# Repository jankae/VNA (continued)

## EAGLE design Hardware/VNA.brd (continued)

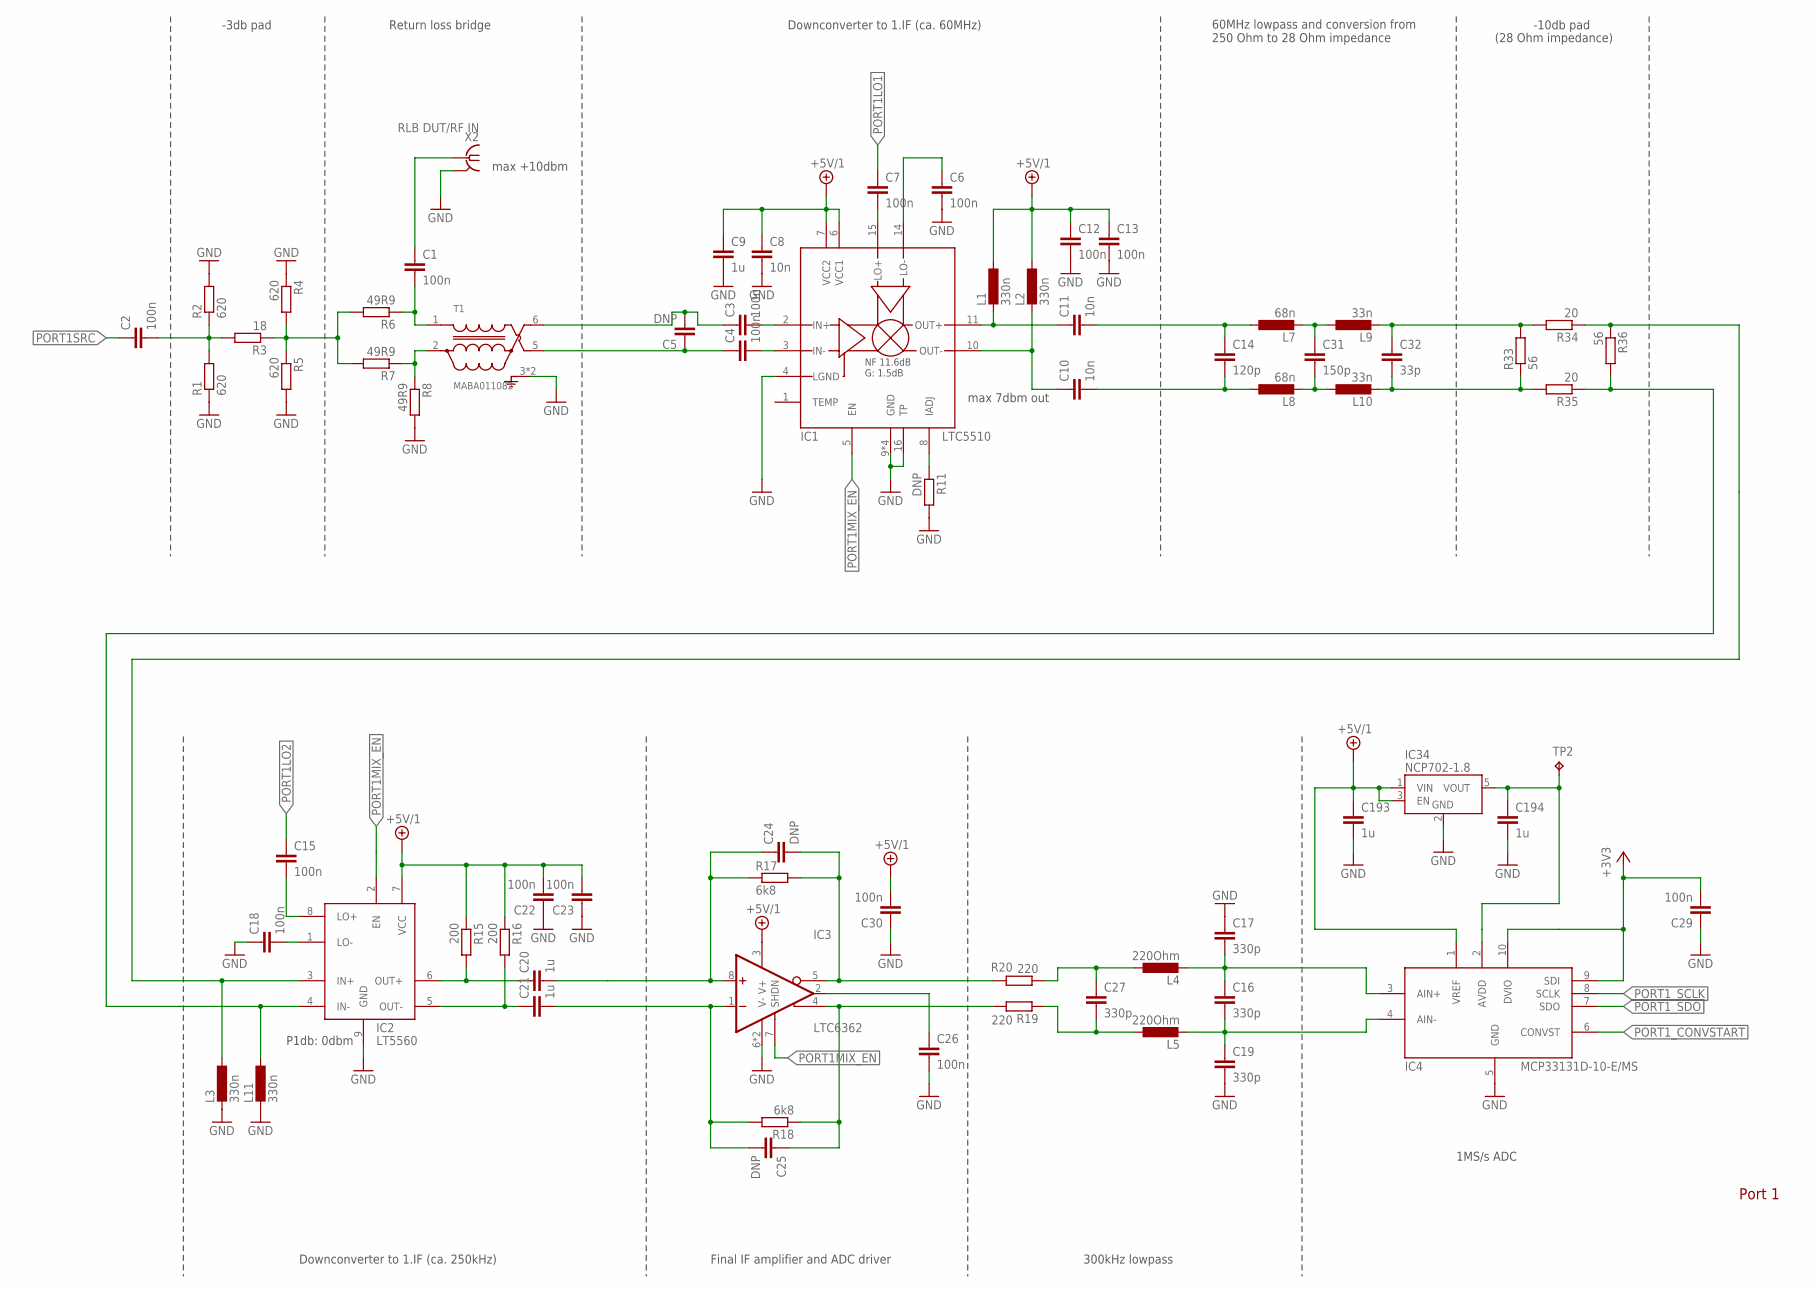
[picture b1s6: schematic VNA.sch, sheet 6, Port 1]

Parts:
C1, C2, C3, C4, C6, C7, C12, C13, C15, C18, C22, C23, C26, C29, C30: 100n; C0603
C5, C24, C25: DNP; C0603
C8, C10, C11: 10n; C0603
C9, C20, C21, C193, C194: 1u; C0603
C14: 120p; C0603
C16, C17, C19, C27: 330p; C0603
C31: 150p; C0603
C32: 33p; C0603
IC1: LTC5510; QFN65P400X400X75-17T215N
IC2: LT5560; SON50P300X300X80-9T165X238
IC3: LTC6362; SON50P300X300X80-9T165X238
IC4: MCP33131D-10-E/MS; SOP50P490X110-10N
IC34: NCP702-1.8; SOT95P240X110-5
L1, L2, L3, L11: 330n; R0603
L4, L5: 220Ohm; R0603
L7, L8: 68n; R0603
L9, L10: 33n; R0603
R1, R2, R4, R5: 620; R0603
R3: 18; R0603
R6, R7, R8: 49R9; R0603
R11: DNP; R0603
R15, R16: 200; R0603
R17, R18: 6k8; R0603
R19, R20: 220; R0603
R33, R36: 56; R0603
R34, R35: 20; R0603
T1: MABA011082; MACOM_BALUN
TP2: TPB1,27; B1,27
X2: RLB DUT/RF IN; J502-ND-142-0711-821/826

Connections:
+3V3: C29.2, IC4.9 (SDI), IC4.10 (DVIO); also elsewhere on the board
+5V/1: C8.1, C9.1, C12.1, C13.1, C22.2, C23.2, C30.2, C193.1, IC1.6 (VCC1), IC1.7 (VCC2), IC2.7 (VCC), IC3.3 (V+), IC4.1 (VREF), IC34.1 (VIN), IC34.3 (EN), L1.1, L2.1, R15.1, R16.1; also elsewhere on the board
GND: C6.2, C8.2, C9.2, C12.2, C13.2, C17.1, C18.1, C19.2, C22.1, C23.1, C26.2, C29.1, C30.1, C193.2, C194.2, IC1.4 (LGND), IC1.9 (GND), IC1.12 (GND), IC1.13 (GND), IC1.16 (TP), IC1.17 (GND), IC2.9 (GND), IC3.6 (V-), IC3.9 (V-), IC4.5 (GND), IC34.2 (GND), L3.2, L11.2, R1.1, R2.2, R4.1, R5.2, R8.2, R11.2, T1.3 (GND), T1.4 (GND), X2.G@1 (2), X2.G@2 (2), X2.G@3 (2), X2.G@4 (2); also elsewhere on the board
unnamed: C2.2, R1.2, R2.1, R3.2
unnamed: R3.1, R4.2, R5.1, R6.2, R7.2
unnamed: C11.2, C14.1, L7.1
unnamed: C1.2, R6.1, T1.1 (PIN1)
unnamed: R7.1, R8.1, T1.2 (PIN2)
unnamed: C1.1, X2.1
unnamed: C3.2, IC1.2 (IN+)
unnamed: C4.2, IC1.3 (IN-)
unnamed: C4.1, C5.1, T1.5 (PIN5)
unnamed: C3.1, C5.2, T1.6 (PIN6)
unnamed: C6.1, IC1.14 (LO-)
unnamed: C7.2, IC1.15 (LO+)
unnamed: C16.1, C17.2, IC4.3 (AIN+), L4.2
unnamed: C11.1, IC1.11 (OUT+), L1.2
unnamed: C10.1, IC1.10 (OUT-), L2.2
unnamed: C10.2, C14.2, L8.1
unnamed: C31.2, L8.2, L10.1
unnamed: C15.2, IC2.8 (LO+)
unnamed: IC1.8 (IADJ), R11.1
unnamed: C16.2, C19.1, IC4.4 (AIN-), L5.2
unnamed: C18.2, IC2.1 (LO-)
unnamed: C20.1, IC2.6 (OUT+), R15.2
unnamed: C21.1, IC2.5 (OUT-), R16.2
unnamed: C25.1, IC3.4 (+OUT), R18.1, R19.2
unnamed: C24.2, IC3.5 (-OUT), R17.2, R20.2
unnamed: C31.1, L7.2, L9.1
unnamed: IC2.3 (IN+), L3.1, R34.1, R36.1
unnamed: C32.1, L9.2, R33.2, R34.2
unnamed: C32.2, L10.2, R33.1, R35.2
unnamed: IC2.4 (IN-), L11.1, R35.1, R36.2
unnamed: C21.2, C25.2, IC3.1 (-IN), R18.2
unnamed: C20.2, C24.1, IC3.8 (+IN), R17.1
unnamed: C194.1, IC4.2 (AVDD), IC34.5 (VOUT), TP2.TP
OUT+: C27.1, L4.1, R20.1
OUT-: C27.2, L5.1, R19.1
OUT_CM: C26.1, IC3.2 (VOCM)
PORT1LO1: C7.1; also elsewhere on the board
PORT1LO2: C15.1; also elsewhere on the board
PORT1MIX_EN: IC1.5 (EN), IC2.2 (EN), IC3.7 (SHDN); also elsewhere on the board
PORT1SRC: C2.1; also elsewhere on the board
PORT1_CONVSTART: IC4.6 (CONVST); also elsewhere on the board
PORT1_SCLK: IC4.8 (SCLK); also elsewhere on the board
PORT1_SDO: IC4.7 (SDO); also elsewhere on the board

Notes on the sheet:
max +10dbm
max 7dbm out
P1db: 0dbm
-3db pad
Return loss bridge
Downconverter to 1.IF (ca. 60MHz)
60MHz lowpass and conversion from 250 Ohm to 28 Ohm impedance
-10db pad
(28 Ohm impedance)
Downconverter to 1.IF (ca. 250kHz)
Final IF amplifier and ADC driver
300kHz lowpass
1MS/s ADC
Port 1

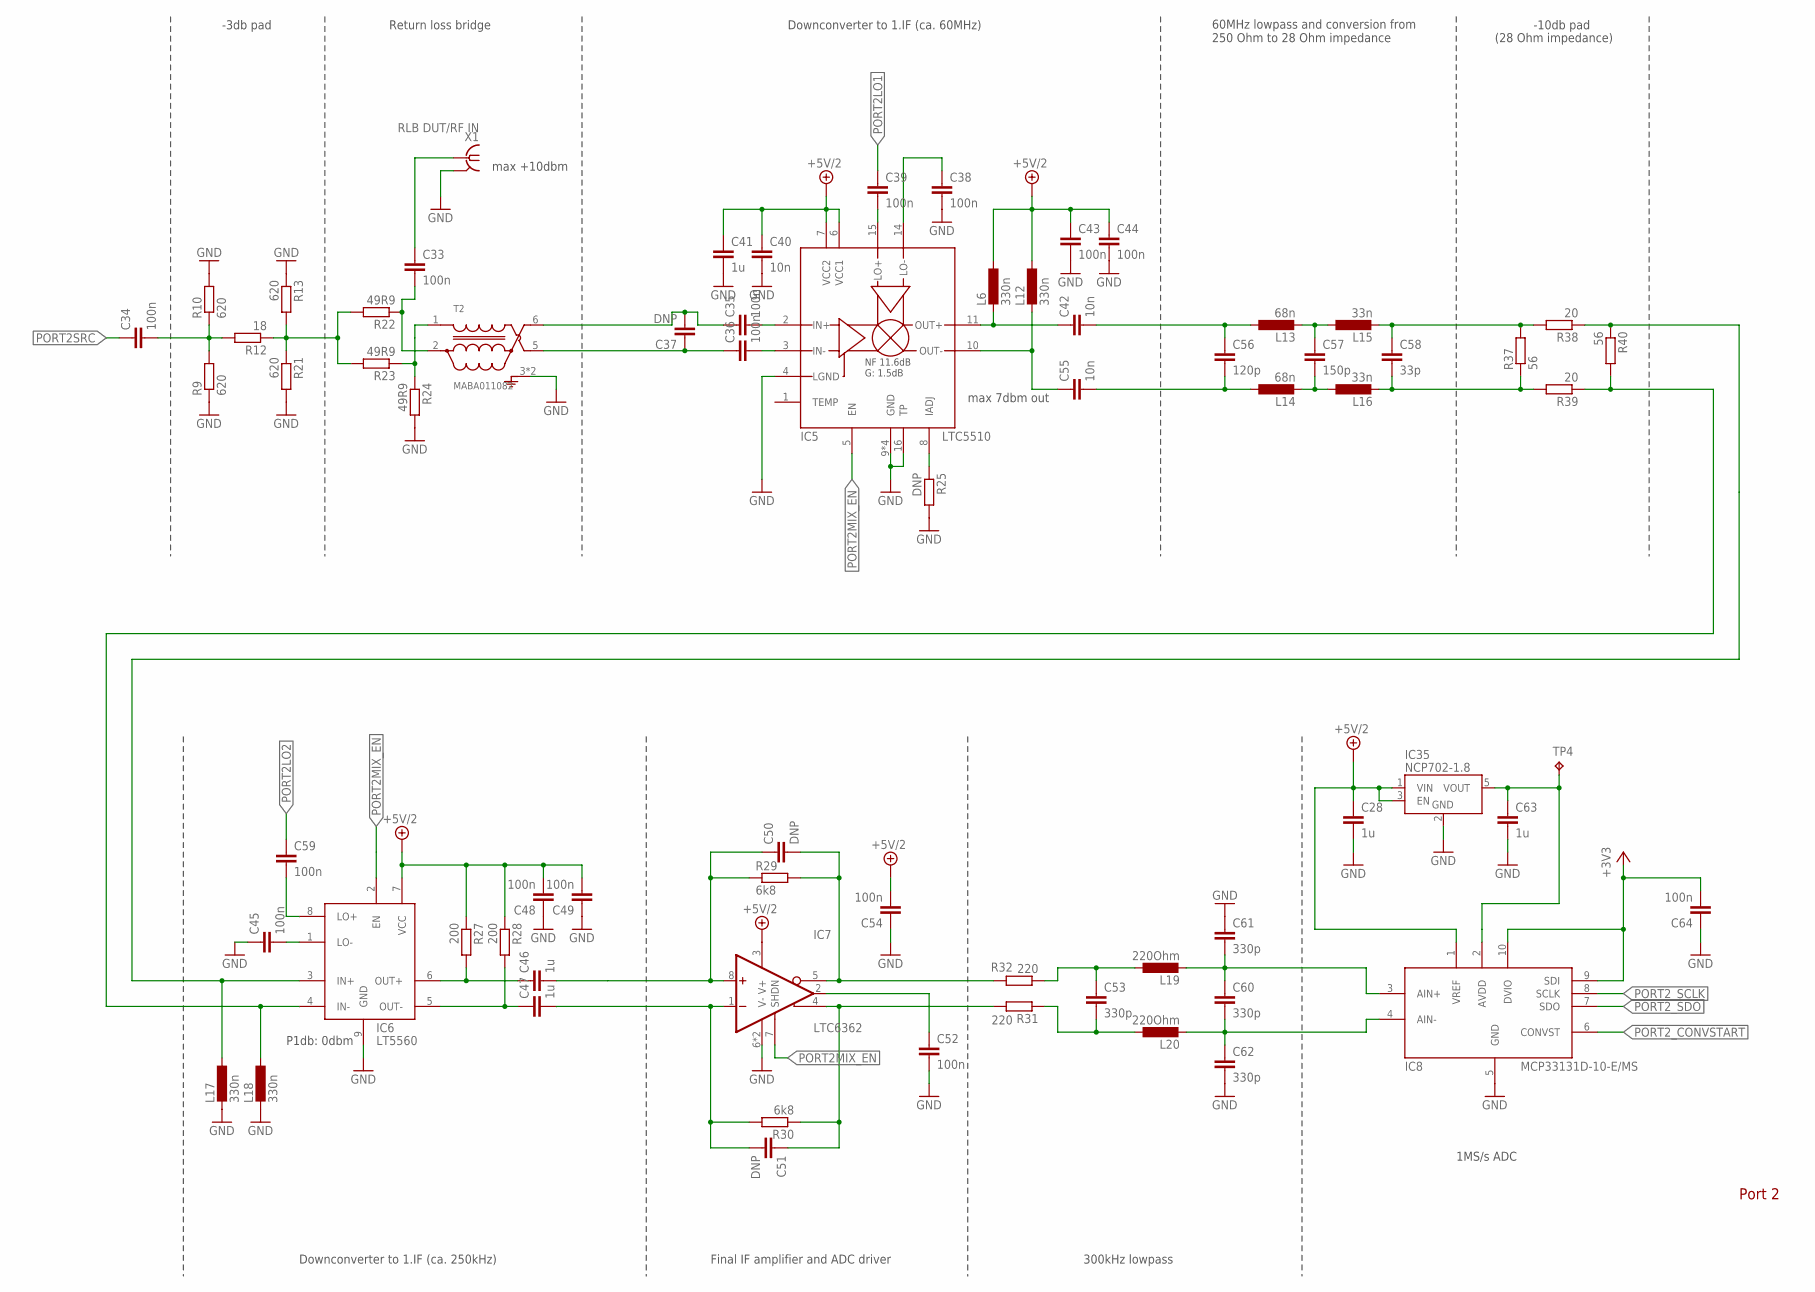
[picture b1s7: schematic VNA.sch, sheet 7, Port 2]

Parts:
C28, C41, C46, C47, C63: 1u; C0603
C33, C34, C35, C36, C38, C39, C43, C44, C45, C48, C49, C52, C54, C59, C64: 100n; C0603
C37, C50, C51: DNP; C0603
C40, C42, C55: 10n; C0603
C53, C60, C61, C62: 330p; C0603
C56: 120p; C0603
C57: 150p; C0603
C58: 33p; C0603
IC5: LTC5510; QFN65P400X400X75-17T215N
IC6: LT5560; SON50P300X300X80-9T165X238
IC7: LTC6362; SON50P300X300X80-9T165X238
IC8: MCP33131D-10-E/MS; SOP50P490X110-10N
IC35: NCP702-1.8; SOT95P240X110-5
L6, L12, L17, L18: 330n; R0603
L13, L14: 68n; R0603
L15, L16: 33n; R0603
L19, L20: 220Ohm; R0603
R9, R10, R13, R21: 620; R0603
R12: 18; R0603
R22, R23, R24: 49R9; R0603
R25: DNP; R0603
R27, R28: 200; R0603
R29, R30: 6k8; R0603
R31, R32: 220; R0603
R37, R40: 56; R0603
R38, R39: 20; R0603
T2: MABA011082; MACOM_BALUN
TP4: TPB1,27; B1,27
X1: RLB DUT/RF IN; J502-ND-142-0711-821/826

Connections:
+3V3: C64.2, IC8.9 (SDI), IC8.10 (DVIO); also elsewhere on the board
+5V/2: C28.1, C40.1, C41.1, C43.1, C44.1, C48.2, C49.2, C54.2, IC5.6 (VCC1), IC5.7 (VCC2), IC6.7 (VCC), IC7.3 (V+), IC8.1 (VREF), IC35.1 (VIN), IC35.3 (EN), L6.1, L12.1, R27.1, R28.1; also elsewhere on the board
GND: C28.2, C38.2, C40.2, C41.2, C43.2, C44.2, C45.1, C48.1, C49.1, C52.2, C54.1, C61.1, C62.2, C63.2, C64.1, IC5.4 (LGND), IC5.9 (GND), IC5.12 (GND), IC5.13 (GND), IC5.16 (TP), IC5.17 (GND), IC6.9 (GND), IC7.6 (V-), IC7.9 (V-), IC8.5 (GND), IC35.2 (GND), L17.2, L18.2, R9.1, R10.2, R13.1, R21.2, R24.2, R25.2, T2.3 (GND), T2.4 (GND), X1.G@1 (2), X1.G@2 (2), X1.G@3 (2), X1.G@4 (2); also elsewhere on the board
unnamed: C34.2, R9.2, R10.1, R12.2
unnamed: R12.1, R13.2, R21.1, R22.2, R23.2
unnamed: C33.2, R22.1, T2.2 (PIN2)
unnamed: R23.1, R24.1, T2.1 (PIN1)
unnamed: C33.1, X1.1
unnamed: C35.2, IC5.2 (IN+)
unnamed: C36.2, IC5.3 (IN-)
unnamed: C36.1, C37.1, T2.5 (PIN5)
unnamed: C35.1, C37.2, T2.6 (PIN6)
unnamed: C38.1, IC5.14 (LO-)
unnamed: C39.2, IC5.15 (LO+)
unnamed: C42.1, IC5.11 (OUT+), L6.2
unnamed: C55.1, IC5.10 (OUT-), L12.2
unnamed: IC5.8 (IADJ), R25.1
unnamed: C45.2, IC6.1 (LO-)
unnamed: C46.1, IC6.6 (OUT+), R27.2
unnamed: C47.1, IC6.5 (OUT-), R28.2
unnamed: C51.1, IC7.4 (+OUT), R30.1, R31.2
unnamed: C50.2, IC7.5 (-OUT), R29.2, R32.2
unnamed: C42.2, C56.1, L13.1
unnamed: C55.2, C56.2, L14.1
unnamed: C57.2, L14.2, L16.1
unnamed: C57.1, L13.2, L15.1
unnamed: IC6.3 (IN+), L17.1, R38.1, R40.1
unnamed: C59.2, IC6.8 (LO+)
unnamed: C60.1, C61.2, IC8.3 (AIN+), L19.2
unnamed: C60.2, C62.1, IC8.4 (AIN-), L20.2
unnamed: C58.1, L15.2, R37.2, R38.2
unnamed: C58.2, L16.2, R37.1, R39.2
unnamed: IC6.4 (IN-), L18.1, R39.1, R40.2
unnamed: C47.2, C51.2, IC7.1 (-IN), R30.2
unnamed: C46.2, C50.1, IC7.8 (+IN), R29.1
unnamed: C63.1, IC8.2 (AVDD), IC35.5 (VOUT), TP4.TP
OUT+1: C53.1, L19.1, R32.1
OUT-1: C53.2, L20.1, R31.1
OUT_CM1: C52.1, IC7.2 (VOCM)
PORT2LO1: C39.1; also elsewhere on the board
PORT2LO2: C59.1; also elsewhere on the board
PORT2MIX_EN: IC5.5 (EN), IC6.2 (EN), IC7.7 (SHDN); also elsewhere on the board
PORT2SRC: C34.1; also elsewhere on the board
PORT2_CONVSTART: IC8.6 (CONVST); also elsewhere on the board
PORT2_SCLK: IC8.8 (SCLK); also elsewhere on the board
PORT2_SDO: IC8.7 (SDO); also elsewhere on the board

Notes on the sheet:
max +10dbm
max 7dbm out
P1db: 0dbm
-3db pad
Return loss bridge
Downconverter to 1.IF (ca. 60MHz)
60MHz lowpass and conversion from 250 Ohm to 28 Ohm impedance
-10db pad
(28 Ohm impedance)
Downconverter to 1.IF (ca. 250kHz)
Final IF amplifier and ADC driver
300kHz lowpass
1MS/s ADC
Port 2

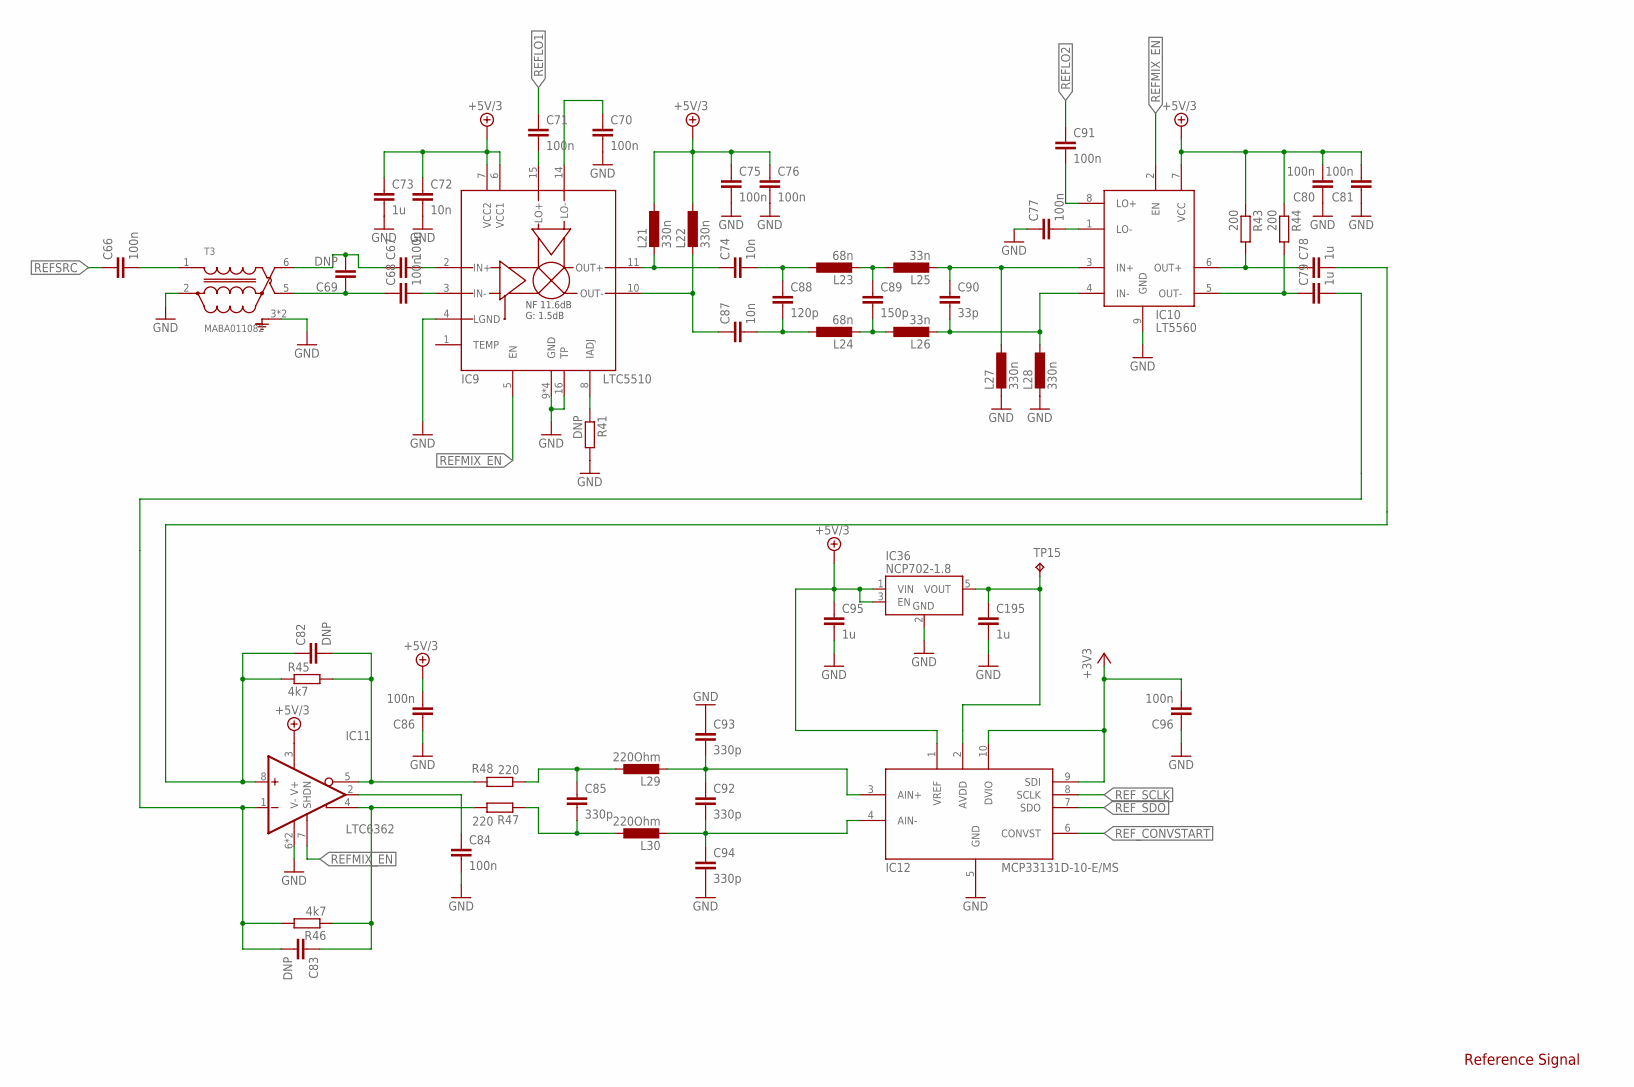
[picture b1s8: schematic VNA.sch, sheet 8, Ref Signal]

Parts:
C66, C67, C68, C70, C71, C75, C76, C77, C80, C81, C84, C86, C91, C96: 100n; C0603
C69, C82, C83: DNP; C0603
C72, C74, C87: 10n; C0603
C73, C78, C79, C95, C195: 1u; C0603
C85, C92, C93, C94: 330p; C0603
C88: 120p; C0603
C89: 150p; C0603
C90: 33p; C0603
IC9: LTC5510; QFN65P400X400X75-17T215N
IC10: LT5560; SON50P300X300X80-9T165X238
IC11: LTC6362; SON50P300X300X80-9T165X238
IC12: MCP33131D-10-E/MS; SOP50P490X110-10N
IC36: NCP702-1.8; SOT95P240X110-5
L21, L22, L27, L28: 330n; R0603
L23, L24: 68n; R0603
L25, L26: 33n; R0603
L29, L30: 220Ohm; R0603
R41: DNP; R0603
R43, R44: 200; R0603
R45, R46: 4k7; R0603
R47, R48: 220; R0603
T3: MABA011082; MACOM_BALUN
TP15: TPB1,27; B1,27

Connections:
+3V3: C96.2, IC12.9 (SDI), IC12.10 (DVIO); also elsewhere on the board
+5V/3: C72.1, C73.1, C75.1, C76.1, C80.2, C81.2, C86.2, C95.1, IC9.6 (VCC1), IC9.7 (VCC2), IC10.7 (VCC), IC11.3 (V+), IC12.1 (VREF), IC36.1 (VIN), IC36.3 (EN), L21.1, L22.1, R43.1, R44.1; also elsewhere on the board
GND: C70.2, C72.2, C73.2, C75.2, C76.2, C77.1, C80.1, C81.1, C84.2, C86.1, C93.1, C94.2, C95.2, C96.1, C195.2, IC9.4 (LGND), IC9.9 (GND), IC9.12 (GND), IC9.13 (GND), IC9.16 (TP), IC9.17 (GND), IC10.9 (GND), IC11.6 (V-), IC11.9 (V-), IC12.5 (GND), IC36.2 (GND), L27.2, L28.2, R41.2, T3.2 (PIN2), T3.3 (GND), T3.4 (GND); also elsewhere on the board
unnamed: C66.2, T3.1 (PIN1)
unnamed: C67.2, IC9.2 (IN+)
unnamed: C68.2, IC9.3 (IN-)
unnamed: C68.1, C69.1, T3.5 (PIN5)
unnamed: C67.1, C69.2, T3.6 (PIN6)
unnamed: C70.1, IC9.14 (LO-)
unnamed: C71.2, IC9.15 (LO+)
unnamed: C74.1, IC9.11 (OUT+), L21.2
unnamed: C87.1, IC9.10 (OUT-), L22.2
unnamed: IC9.8 (IADJ), R41.1
unnamed: C77.2, IC10.1 (LO-)
unnamed: C78.1, IC10.6 (OUT+), R43.2
unnamed: C79.1, IC10.5 (OUT-), R44.2
unnamed: C78.2, C82.1, IC11.8 (+IN), R45.1
unnamed: C79.2, C83.2, IC11.1 (-IN), R46.2
unnamed: C83.1, IC11.4 (+OUT), R46.1, R47.2
unnamed: C82.2, IC11.5 (-OUT), R45.2, R48.2
unnamed: C74.2, C88.1, L23.1
unnamed: C87.2, C88.2, L24.1
unnamed: C89.2, L24.2, L26.1
unnamed: C89.1, L23.2, L25.1
unnamed: C90.1, IC10.3 (IN+), L25.2, L27.1
unnamed: C90.2, IC10.4 (IN-), L26.2, L28.1
unnamed: C91.2, IC10.8 (LO+)
unnamed: C92.1, C93.2, IC12.3 (AIN+), L29.2
unnamed: C92.2, C94.1, IC12.4 (AIN-), L30.2
unnamed: C195.1, IC12.2 (AVDD), IC36.5 (VOUT), TP15.TP
OUT+2: C85.1, L29.1, R48.1
OUT-2: C85.2, L30.1, R47.1
OUT_CM2: C84.1, IC11.2 (VOCM)
REFLO1: C71.1; also elsewhere on the board
REFLO2: C91.1; also elsewhere on the board
REFMIX_EN: IC9.5 (EN), IC10.2 (EN), IC11.7 (SHDN); also elsewhere on the board
REFSRC: C66.1; also elsewhere on the board
REF_CONVSTART: IC12.6 (CONVST); also elsewhere on the board
REF_SCLK: IC12.8 (SCLK); also elsewhere on the board
REF_SDO: IC12.7 (SDO); also elsewhere on the board

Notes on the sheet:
Reference Signal

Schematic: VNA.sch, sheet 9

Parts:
C191, C192, C203, C204, C205, C206, C207, C208, C209, C210, C211: 100n; C0603
IC33: STM32L432KC; QFN50P500X500X100-33T345N
JP1: PINHD-1X6; 1X06
JTAG: ML10
R76, R88, R91: 22; R0603
R89: 1k5; R0603
R90, R92, R93, R94, R95, R111: 10k; R0603
U2: 6SLX9TQG144; TQ144
U4: W25Q16BVSN; SO08
X4: MINI-USB-SCHIELD-32005-301; 32005-301

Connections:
+3V3: C191.1, C192.1, C203.1, C204.1, C205.1, C206.1, C207.1, IC33.1 (VDD1), IC33.5 (VDDA/VREF+), IC33.17 (VDD2), JP1.1, JTAG.4, R90.2, R92.2, R93.2, R94.2, R95.2, U2.P20 (VCCAUX), U2.P36 (VCCAUX), U2.P42 (VCCO_2), U2.P53 (VCCAUX), U2.P63 (VCCO_2), U2.P69 (IO_L1N_M0_CMPMISO_2), U2.P90 (VCCAUX), U2.P129 (VCCAUX), U4.3 (!WP!), U4.7 (!HOLD!), U4.8 (VCC); also elsewhere on the board
FLACH_MOSI: U2.P64 (IO_L3N_MOSI_CSI_B_MISO0_2), U4.5 (DI)
FLASH_CLK: U2.P70 (IO_L1P_CCLK_2), U4.6 (CLK)
FLASH_CS: U2.P38 (IO_L65N_CSO_B_2), U4.1 (!CS!)
FLASH_MISO: R91.1, U4.2 (DO)
FPGA_RESET: IC33.7 (PA1/TIM2_CH2/SPI1_SCK), U2.P48 (IO_L48P_D7_2)
GND: C191.2, C192.2, C203.2, C204.2, C205.2, C206.2, C207.2, C208.2, C209.2, C210.2, C211.2, IC33.16 (VSS1), IC33.31 (BOOT0), IC33.32 (VSS2), IC33.33 (EP), JP1.3, JTAG.2, JTAG.10, R111.1, U2.P3 (GND), U2.P13 (GND), U2.P25 (GND), U2.P49 (GND), U2.P54 (GND), U2.P60 (IO_L13P_M1_2), U2.P68 (GND), U2.P73 (SUSPEND), U2.P77 (GND), U2.P91 (GND), U2.P96 (GND), U2.P108 (GND), U2.P113 (GND), U2.P130 (GND), U2.P136 (GND), U4.4 (GND), X4.5, X4.M1 (S1), X4.M2 (S2), X4.M3 (S3), X4.M4 (S4); also elsewhere on the board
MCU_AUX1: IC33.2 (PC14-OSC32_IN), U2.P55 (IO_L30N_GCLK0_USERCCLK_2)
MCU_AUX2: IC33.3 (PC15-OSC32_OUT), U2.P51 (IO_L31P_GCLK31_D14_2)
MCU_AUX3: IC33.6 (PA0/CK_IN/TIM2_CH1), U2.P50 (IO_L31N_GCLK30_D15_2)
MCU_INTR: IC33.30 (PB7/I2C1_SDA/USART1_RX), U2.P57 (IO_L14N_D12_2)
MCU_MISO: IC33.27 (PB4/I2C3_SDA/SPI1_MISO/SPI3_MISO), U2.P61 (IO_L12N_D2_MISO3_2)
MCU_MOSI: IC33.28 (PB5/SPI1_MOSI/SPI3_MOSI), U2.P59 (IO_L13N_D10_2)
MCU_NSS: IC33.29 (PB6/I2C1_SCL/USART1_TX), U2.P58 (IO_L14P_D11_2)
MCU_SCK: IC33.26 (PB3/TIM2_CH2/SPI1_SCK/SPI3_SCK), U2.P56 (IO_L30P_GCLK1_D13_2)
unnamed: JTAG.3, U2.P106 (TDO)
unnamed: JTAG.5, U2.P107 (TMS)
unnamed: JTAG.9, U2.P110 (TDI)
unnamed: JTAG.1, U2.P109 (TCK)
unnamed: R88.1, X4.2
unnamed: R76.2, R89.2, X4.3
unnamed: IC33.21 (PA11/TIM1_CH4/SPI1_MISO/CAN1_RX/USB_DM), R88.2
unnamed: IC33.22 (PA12/SPI1_MOSI/CAN1_TX/USB_DP), R76.1
unnamed: IC33.25 (PA15/TIM2_CH1/USART2_RX/SPI1_NSS/SPI3_N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), R89.1
unnamed: IC33.24 (PA14/SWCLK), JP1.2
unnamed: IC33.23 (PA13/SWDIO), JP1.4
unnamed: IC33.4 (NRST), JP1.5
unnamed: IC33.8 (PA2/TIM2_CH3/USART2_TX), JP1.6
unnamed: R92.1, U2.P71 (DONE_2)
unnamed: R93.1, U2.P39 (IO_L65P_INIT_B_2)
unnamed: R94.1, U2.P37 (PROGRAM_B_2)
unnamed: R91.2, U2.P65 (IO_L3P_D0_DIN_MISO_MISO1_2)
PORT2MIX_EN: R111.2, U2.P44 (IO_L62P_D5_2); also elsewhere on the board
PORT2_CONVSTART: U2.P47 (IO_L48N_RDWR_B_VREF_2); also elsewhere on the board
PORT2_SCLK: U2.P45 (IO_L49N_D4_2); also elsewhere on the board
PORT2_SDO: U2.P46 (IO_L49P_D3_2); also elsewhere on the board
REF_CONVSTART: U2.P43 (IO_L62N_D6_2); also elsewhere on the board
REF_SCLK: U2.P40 (IO_L64N_D9_2); also elsewhere on the board
REF_SDO: U2.P41 (IO_L64P_D8_2); also elsewhere on the board
SCL: IC33.19 (PA9/TIM1_CH2/I2C1_SCL/USART1_TX), R90.1; also elsewhere on the board
SDA: IC33.20 (PA10/TIM1_CH3/I2C1_SDA/USART1_RX), R95.1; also elsewhere on the board
SWITCHING_SYNC: U2.P62 (IO_L12P_D1_MISO2_2); also elsewhere on the board
VCCINT: C208.1, C209.1, C210.1, C211.1, U2.P19 (VCCINT), U2.P28 (VCCINT), U2.P52 (VCCINT), U2.P89 (VCCINT), U2.P128 (VCCINT); also elsewhere on the board

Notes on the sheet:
FPGA + MCU Connections
FPGA sets all pins as pullups while indirectly programming the flash. This disables the power supply through the switching_sync pin. As this behaviour is caused by the xc6slx9_spi.cor (and not changable with HSWAPEN), the only work-around is to cut the switching_sync connection while programming th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

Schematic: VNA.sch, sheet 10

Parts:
LED1, LED2, LED3, LED4, LED5, LED6, LED7, LED8, LED9: LEDCHIPLED_0603; CHIPLED_0603
R14, R26, R42, R105, R106, R107, R108, R109, R110: 330; R0603
R96: 22; R0603
R112, R113: 10k; R0603
U2: 6SLX9TQG144; TQ144

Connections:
+3V3: LED1.A, LED2.A, LED3.A, LED4.A, LED5.A, LED6.A, LED7.A, LED8.A, LED9.A, U2.P4 (VCCO_3), U2.P18 (VCCO_3), U2.P31 (VCCO_3), U2.P76 (VCCO_1), U2.P86 (VCCO_1), U2.P103 (VCCO_1), U2.P122 (VCCO_0), U2.P125 (VCCO_0), U2.P135 (VCCO_0); also elsewhere on the board
AMP_PWDN: U2.P24 (IO_L41P_GCLK27_3); also elsewhere on the board
ATT_D0: U2.P34 (IO_L1N_VREF_3); also elsewhere on the board
ATT_D1: U2.P33 (IO_L2P_3); also elsewhere on the board
ATT_D2: U2.P32 (IO_L2N_3); also elsewhere on the board
ATT_D3: U2.P30 (IO_L36P_3); also elsewhere on the board
ATT_D4: U2.P29 (IO_L36N_3); also elsewhere on the board
ATT_D5: U2.P27 (IO_L37P_3); also elsewhere on the board
ATT_D6: U2.P26 (IO_L37N_3); also elsewhere on the board
BAND_SELECT: U2.P22 (IO_L42P_GCLK25_TRDY2_3); also elsewhere on the board
FILT_IN_C1: U2.P15 (IO_L44P_GCLK21_3); also elsewhere on the board
FILT_IN_C2: U2.P16 (IO_L43N_GCLK22_IRDY2_3); also elsewhere on the board
FILT_OUT_C1: U2.P21 (IO_L42N_GCLK24_3); also elsewhere on the board
FILT_OUT_C2: U2.P17 (IO_L43P_GCLK23_3); also elsewhere on the board
FPGA_CLK: R96.1; also elsewhere on the board
GND: R110.2, R112.1, R113.1; also elsewhere on the board
LO1_CE: U2.P138 (IO_L4P_0); also elsewhere on the board
LO1_CLK: U2.P141 (IO_L2N_0); also elsewhere on the board
LO1_LD: U2.P142 (IO_L2P_0); also elsewhere on the board
LO1_LE: U2.P139 (IO_L3N_0); also elsewhere on the board
LO1_MOSI: U2.P140 (IO_L3P_0); also elsewhere on the board
LO1_MUX: U2.P144 (IO_L1P_HSWAPEN_0); also elsewhere on the board
LO1_RF_EN: U2.P143 (IO_L1N_VREF_0); also elsewhere on the board
unnamed: R96.2, U2.P14 (IO_L44N_GCLK20_3)
unnamed: LED9.C, R14.1
unnamed: LED8.C, R26.1
unnamed: LED7.C, R42.1
unnamed: LED6.C, R105.1
unnamed: LED5.C, R106.1
unnamed: LED4.C, R107.1
unnamed: LED3.C, R108.1
unnamed: LED2.C, R109.1
unnamed: LED1.C, R110.1
unnamed: R14.2, U2.P105 (IO_L1P_1)
unnamed: R26.2, U2.P104 (IO_L1N_VREF_1)
unnamed: R42.2, U2.P99 (IO_L33N_1)
unnamed: R105.2, U2.P94 (IO_L40N_GCLK10_1)
unnamed: R106.2, U2.P85 (IO_L43P_GCLK5_1)
unnamed: R107.2, U2.P82 (IO_L45N_1)
unnamed: R108.2, U2.P75 (IO_L74P_AWAKE_1)
unnamed: R109.2, U2.P118 (IO_L63N_SCP6_0)
PORT1MIX_EN: R112.2, U2.P137 (IO_L4N_0); also elsewhere on the board
PORT1_CONVSTART: U2.P134 (IO_L34P_GCLK19_0); also elsewhere on the board
PORT1_SCLK: U2.P132 (IO_L35P_GCLK17_0); also elsewhere on the board
PORT1_SDO: U2.P133 (IO_L34N_GCLK18_0); also elsewhere on the board
PORT_SELECT: U2.P23 (IO_L41N_GCLK26_3); also elsewhere on the board
REFMIX_EN: R113.2, U2.P35 (IO_L1P_3); also elsewhere on the board
SCL: U2.P6 (IO_L52P_3); also elsewhere on the board
SDA: U2.P9 (IO_L50N_3); also elsewhere on the board
SOURCE_CE: U2.P1 (IO_L83N_VREF_3); also elsewhere on the board
SOURCE_CLK: U2.P7 (IO_L51N_3); also elsewhere on the board
SOURCE_LD: U2.P10 (IO_L50P_3); also elsewhere on the board
SOURCE_LE: U2.P2 (IO_L83P_3); also elsewhere on the board
SOURCE_MOSI: U2.P5 (IO_L52N_3); also elsewhere on the board
SOURCE_MUX: U2.P8 (IO_L51P_3); also elsewhere on the board
SOURCE_RF_EN: U2.P11 (IO_L49N_3); also elsewhere on the board

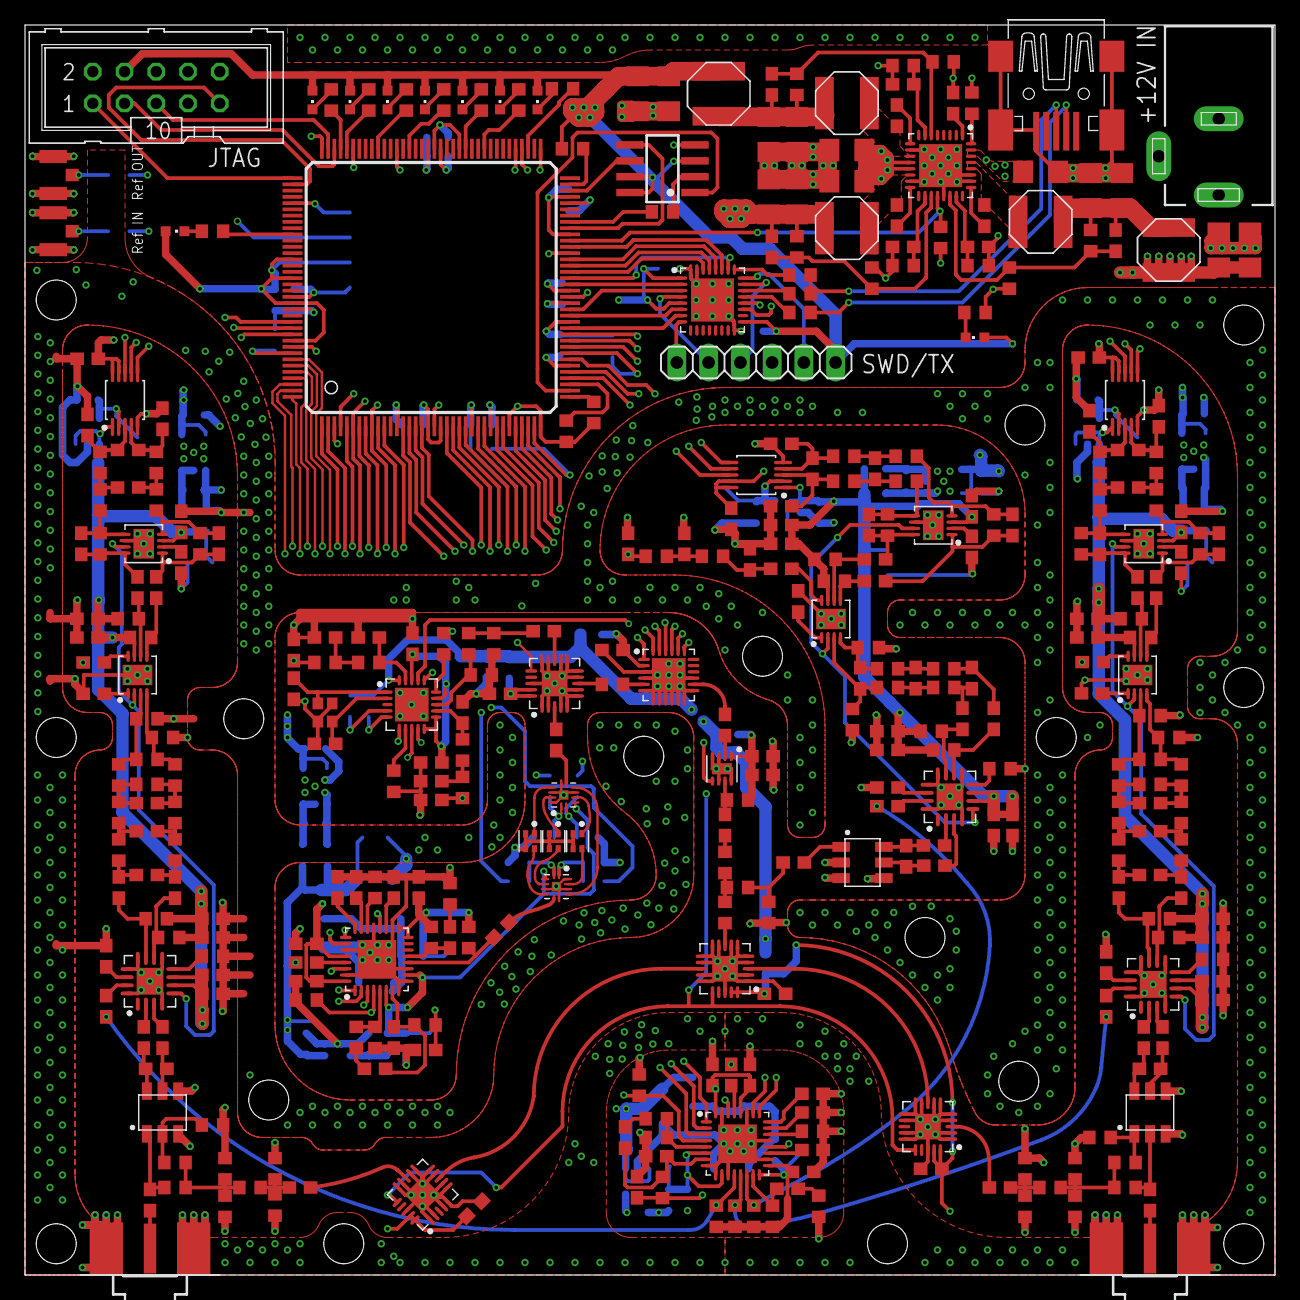
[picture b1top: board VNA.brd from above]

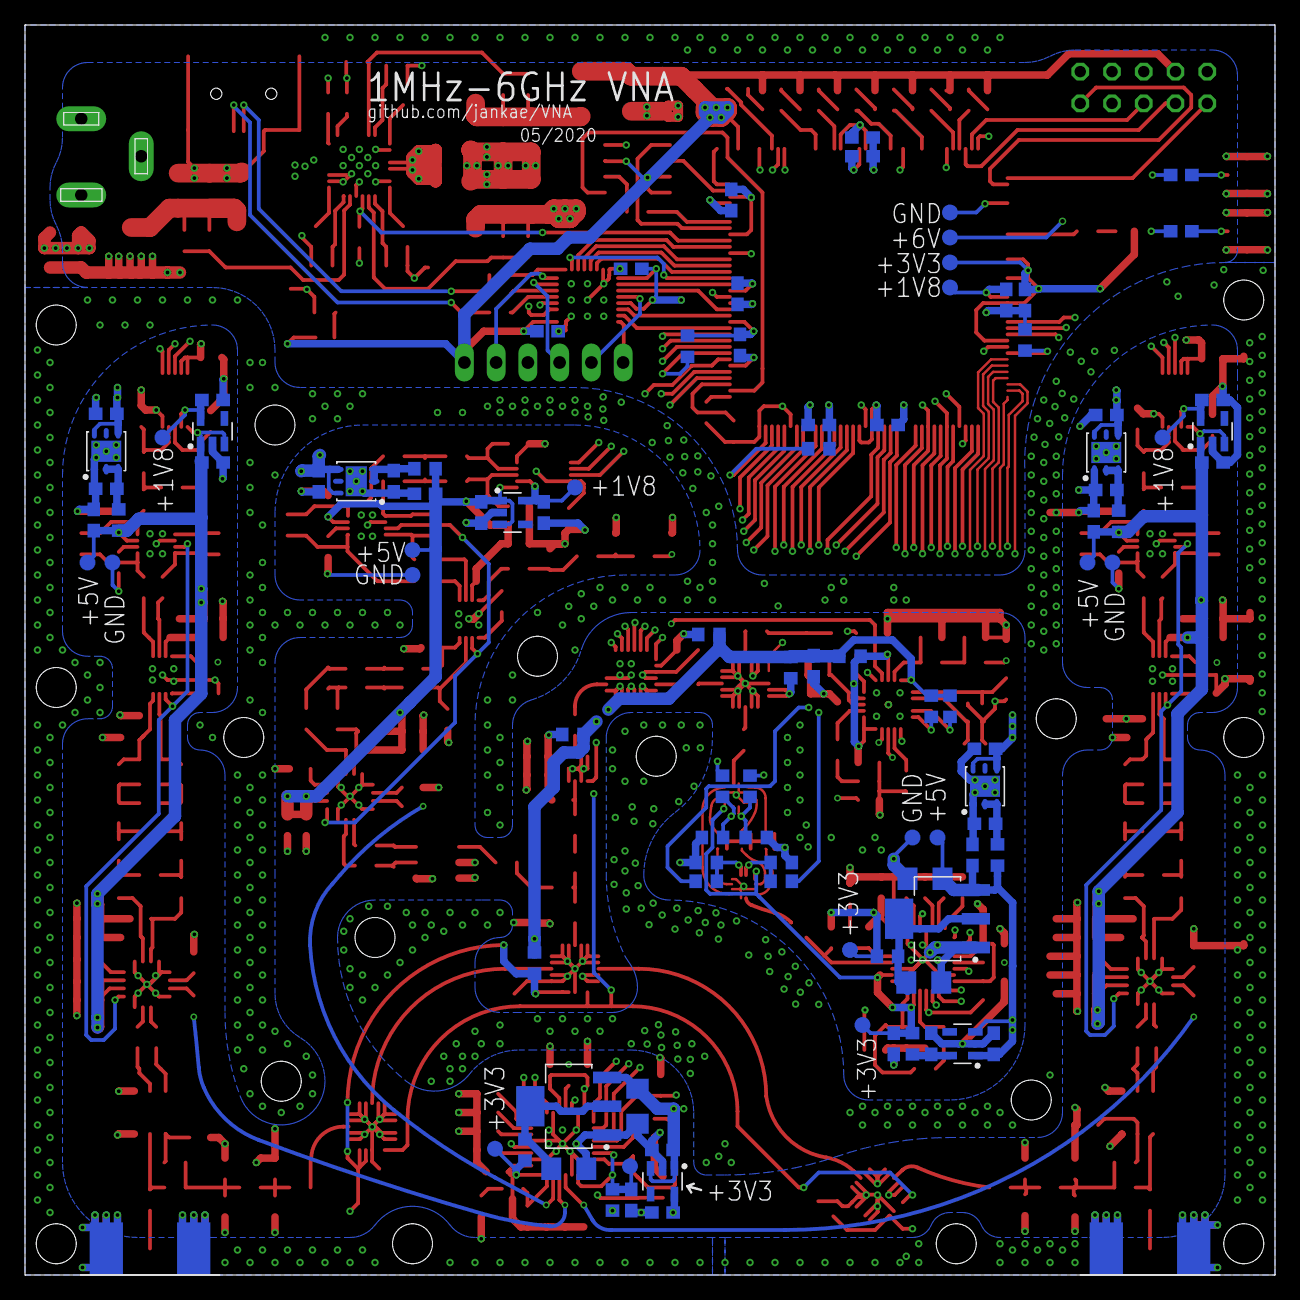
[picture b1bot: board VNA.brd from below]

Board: 4 copper layers, 100.0 x 100.0 mm, 453 parts (98 on the bottom side), 310 nets.

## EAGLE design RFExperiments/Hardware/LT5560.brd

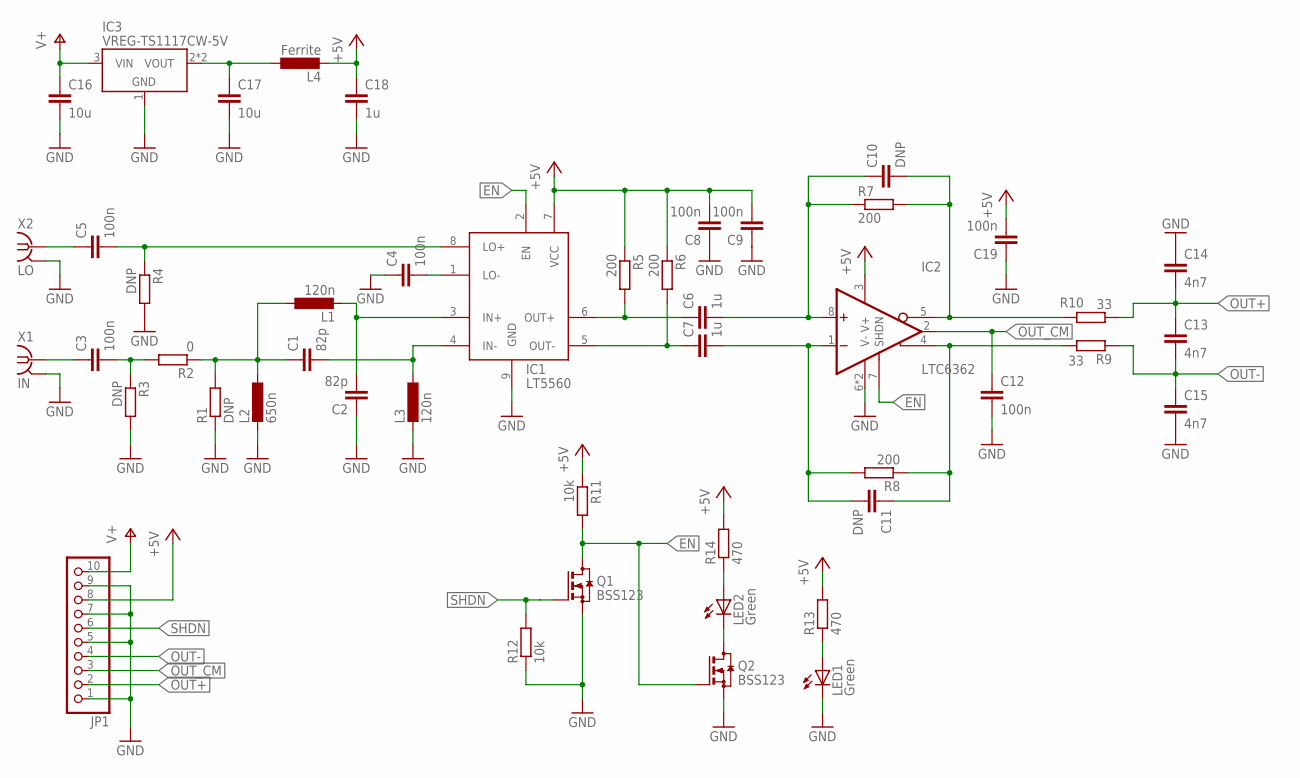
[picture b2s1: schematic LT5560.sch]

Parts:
C1, C2: 82p; C0603
C3, C4, C5, C8, C9, C12, C19: 100n; C0603
C6, C7, C18: 1u; C0603
C10, C11: DNP; C0603
C13, C14, C15: 4n7; C0603
C16, C17: 10u; C1206
IC1: LT5560; SON50P300X300X80-9T165X238
IC2: LTC6362; SON50P300X300X80-9T165X238
IC3: VREG-TS1117CW-5V; SOT223
JP1: PINHD-1X10/90; 1X10/90
L1, L3: 120n; R0603
L2: 650n; R0603
L4: Ferrite; R0603
LED1, LED2: Green; LED_SML0603
Q1, Q2: BSS123; SOT23
R1, R3, R4: DNP; R0603
R2: 0; R0603
R5, R6, R7, R8: 200; R0603
R9, R10: 33; R0603
R11, R12: 10k; R0603
R13, R14: 470; R0603
X1: IN; J502-ND-142-0711-821/826
X2: LO; J502-ND-142-0711-821/826

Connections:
+5V: C8.2, C9.2, C18.1, C19.2, IC1.7 (VCC), IC2.3 (V+), JP1.8, L4.2, R5.1, R6.1, R11.1, R13.2, R14.2
EN: IC1.2 (EN), IC2.7 (SHDN), Q1.3 (D), Q2.1 (G), R11.2
GND: C2.1, C4.1, C8.1, C9.1, C12.2, C14.1, C15.2, C16.2, C17.2, C18.2, C19.1, IC1.9 (GND), IC2.6 (V-), IC2.9 (V-), IC3.1 (GND), JP1.1, JP1.5, JP1.7, JP1.9, L2.2, L3.2, LED1.C, Q1.2 (S), Q2.2 (S), R1.1, R3.2, R4.2, R12.1, X1.G@1 (2), X1.G@2 (2), X1.G@3 (2), X1.G@4 (2), X2.G@1 (2), X2.G@2 (2), X2.G@3 (2), X2.G@4 (2)
GND1: LED2.C, Q2.3 (D)
unnamed: C1.2, IC1.4 (IN-), L3.1
unnamed: C2.2, IC1.3 (IN+), L1.2
unnamed: C1.1, L1.1, L2.1, R1.2, R2.1
unnamed: C3.1, X1.1
unnamed: C3.2, R2.2, R3.1
unnamed: C4.2, IC1.1 (LO-)
unnamed: C5.2, IC1.8 (LO+), R4.1
unnamed: C5.1, X2.1
unnamed: C11.1, IC2.4 (+OUT), R8.1, R9.2
unnamed: C6.1, IC1.6 (OUT+), R5.2
unnamed: C7.1, IC1.5 (OUT-), R6.2
unnamed: C6.2, C10.1, IC2.8 (+IN), R7.1
unnamed: C7.2, C11.2, IC2.1 (-IN), R8.2
unnamed: C10.2, IC2.5 (-OUT), R7.2, R10.2
unnamed: C17.1, IC3.2 (VOUT), IC3.4 (VOUT), L4.1
unnamed: LED2.A, R14.1
unnamed: LED1.A, R13.1
OUT+: C13.1, C14.2, JP1.2, R10.1
OUT-: C13.2, C15.1, JP1.4, R9.1
OUT_CM: C12.1, IC2.2 (VOCM), JP1.3
SHDN: JP1.6, Q1.1 (G), R12.2
V+: C16.1, IC3.3 (VIN), JP1.10
